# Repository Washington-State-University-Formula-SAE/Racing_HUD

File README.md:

# wsuRacing_wheelDisplay
Files for the Wazzu Racing Heads up display

Features:

ECU - Arduino CAN comuunicaiton
Display for important run time info
I/O Availible for DATA_AC to use

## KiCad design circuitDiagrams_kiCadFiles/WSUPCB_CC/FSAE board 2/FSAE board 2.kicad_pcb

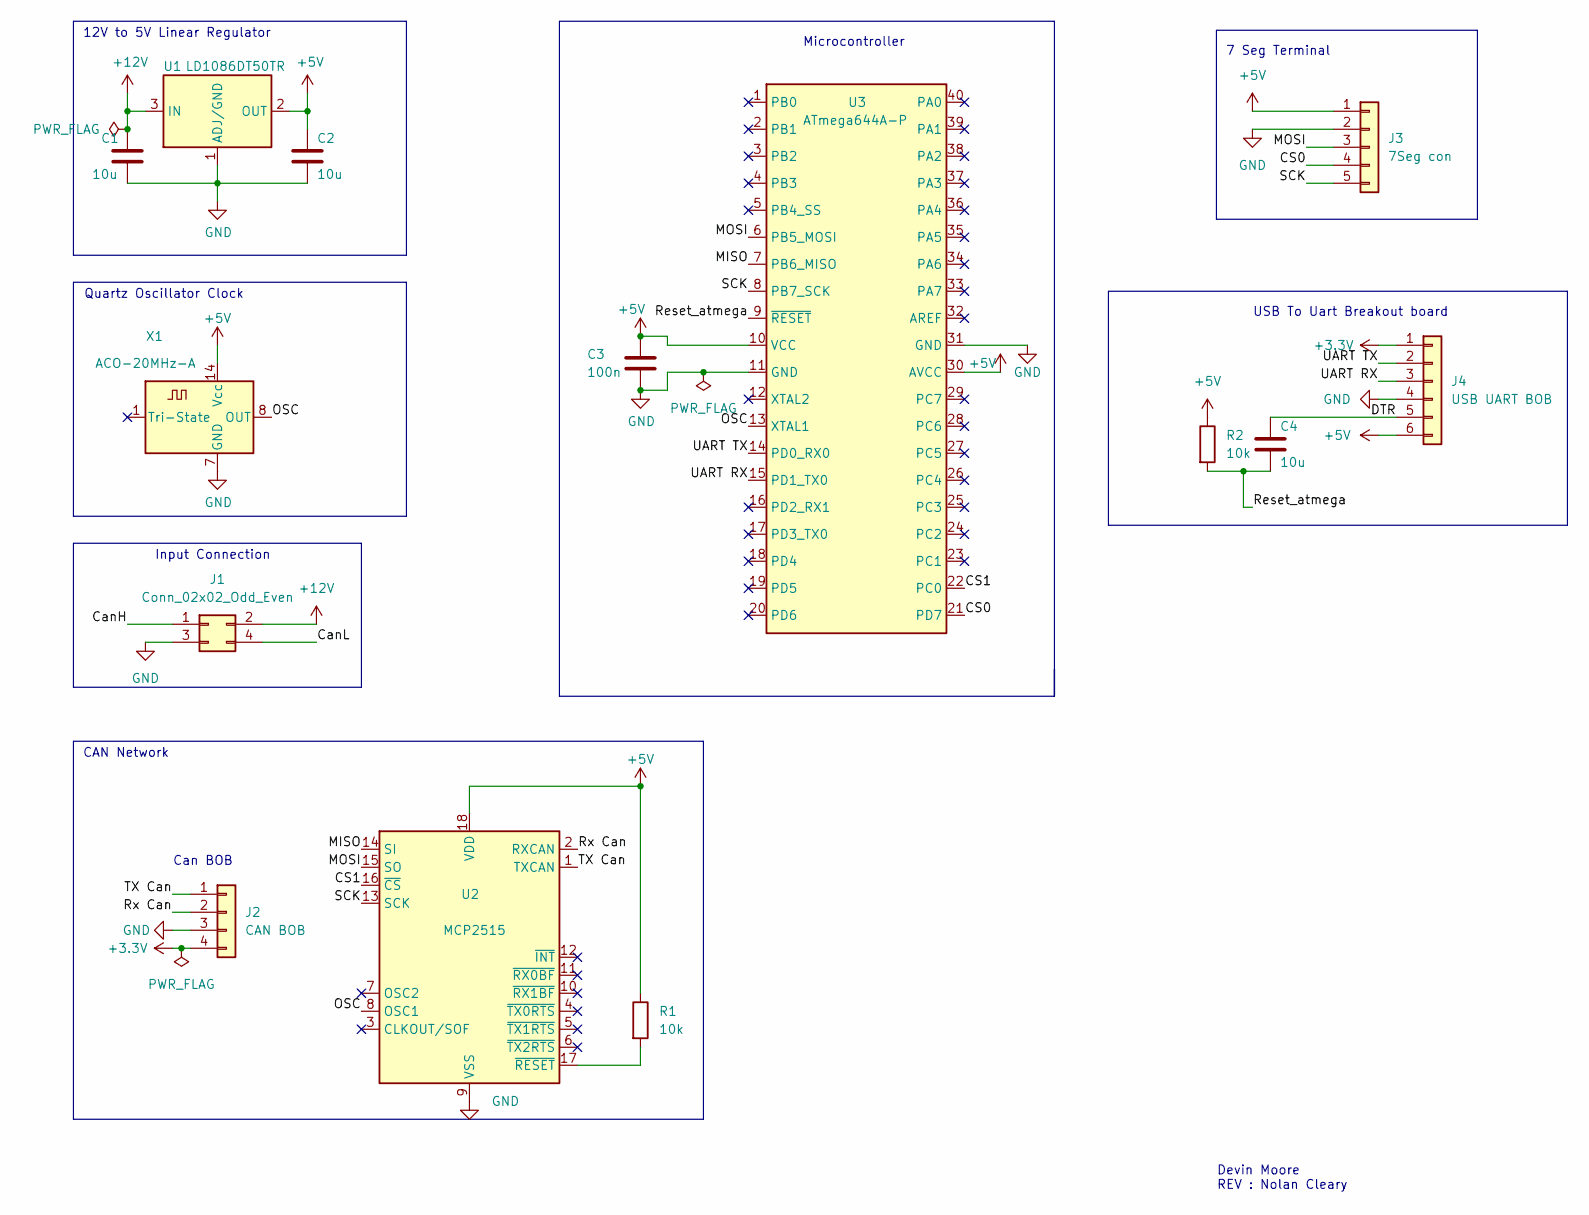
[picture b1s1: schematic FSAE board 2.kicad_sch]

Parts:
C1, C2, C4: 10u; C_Disc_D3.0mm_W1.6mm_P2.50mm
C3: 100n; C_Disc_D3.0mm_W1.6mm_P2.50mm
J1: Conn_02x02_Odd_Even; PinSocket_2x02_P2.00mm_Vertical
J2: CAN BOB; PinHeader_1x04_P2.00mm_Vertical
J3: 7Seg con; PinSocket_1x05_P2.00mm_Vertical
J4: USB UART BOB; PinHeader_1x06_P2.00mm_Vertical
R1, R2: 10k; R_Axial_DIN0204_L3.6mm_D1.6mm_P5.08mm_Horizontal
U1: LD1086DT50TR; TO-252-2
U2: MCP2515; DIP-18_W7.62mm_Socket
U3: ATmega644A-P; DIP-40_W15.24mm
X1: ACO-20MHz-A; Oscillator_DIP-14

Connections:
+3V3: J2.4, J4.1
+5V: C2.1, C3.1, J3.1, J4.6, R1.1, R2.1, U1.2 (OUT), U2.18 (VDD), U3.10 (VCC), U3.30 (AVCC), X1.14 (Vcc)
+12V: C1.1, J1.2, U1.3 (IN)
/CS0: J3.4, U3.21 (PD7)
/CS1: U2.16 (~CS), U3.22 (PC0)
/CanH: J1.1
/CanL: J1.4
/DTR: C4.1, J4.5
/MISO: U2.14 (SI), U3.7 (PB6_MISO)
/MOSI: J3.3, U2.15 (SO), U3.6 (PB5_MOSI)
/OSC: U2.8 (OSC1), U3.13 (XTAL1), X1.8 (OUT)
/Reset_atmega: C4.2, R2.2, U3.9 (~RESET)
/Rx Can: J2.2, U2.2 (RXCAN)
/SCK: J3.5, U2.13 (SCK), U3.8 (PB7_SCK)
/TX Can: J2.1, U2.1 (TXCAN)
/UART RX: J4.3, U3.15 (PD1_TX0)
/UART TX: J4.2, U3.14 (PD0_RX0)
GND: C1.2, C2.2, C3.2, J1.3, J2.3, J3.2, J4.4, U1.1 (ADJ/GND), U2.9 (VSS), U3.11 (GND), U3.31 (GND), X1.7 (GND)
unnamed: R1.2, U2.17 (~RESET)

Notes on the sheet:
7 Seg Terminal
Input Connection
Microcontroller
Devin Moore REV : Nolan Cleary
Quartz Oscillator Clock
CAN Network
12V to 5V Linear Regulator
USB To Uart Breakout board
Can BOB

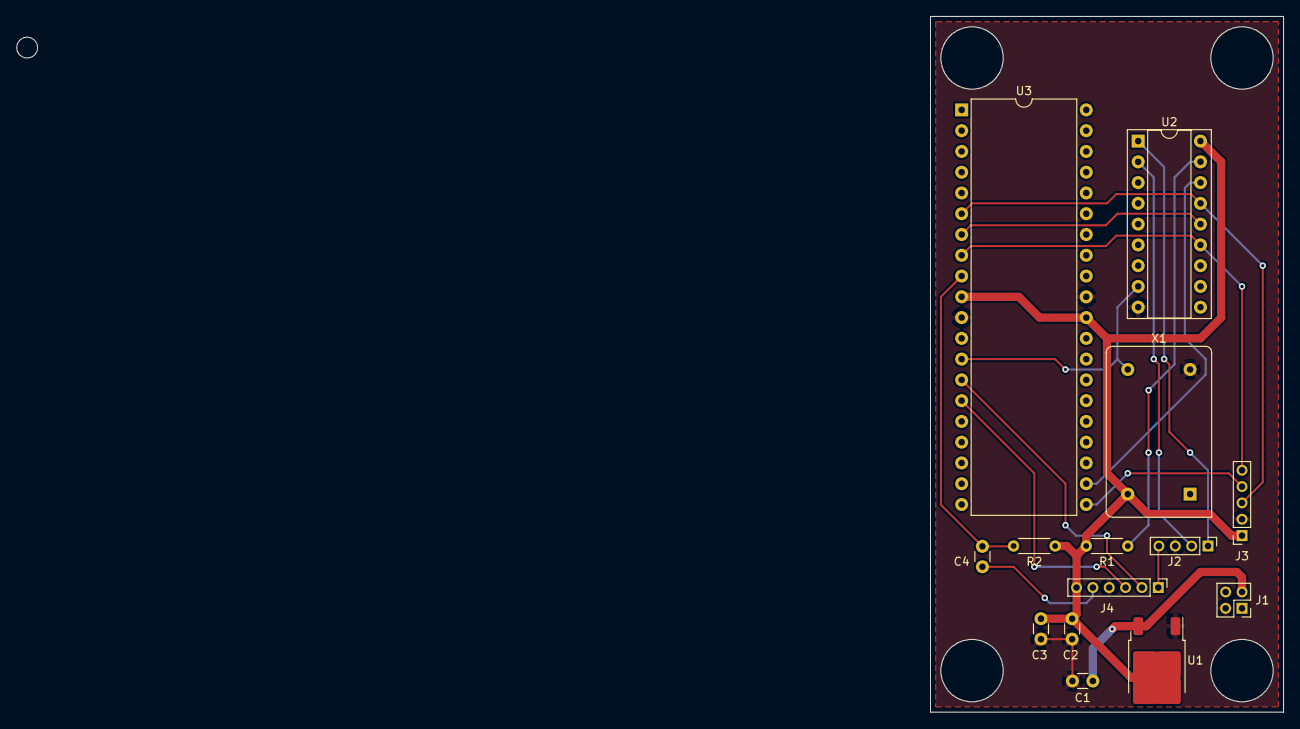
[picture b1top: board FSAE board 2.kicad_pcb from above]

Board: 2 copper layers, 43.2 x 85.1 mm, 14 parts (0 on the bottom side), 17 nets.

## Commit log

2022-10-22 Merging older files
2023-01-28 Updated schematics
2023-10-13 Create area for Carson PCB Designs
